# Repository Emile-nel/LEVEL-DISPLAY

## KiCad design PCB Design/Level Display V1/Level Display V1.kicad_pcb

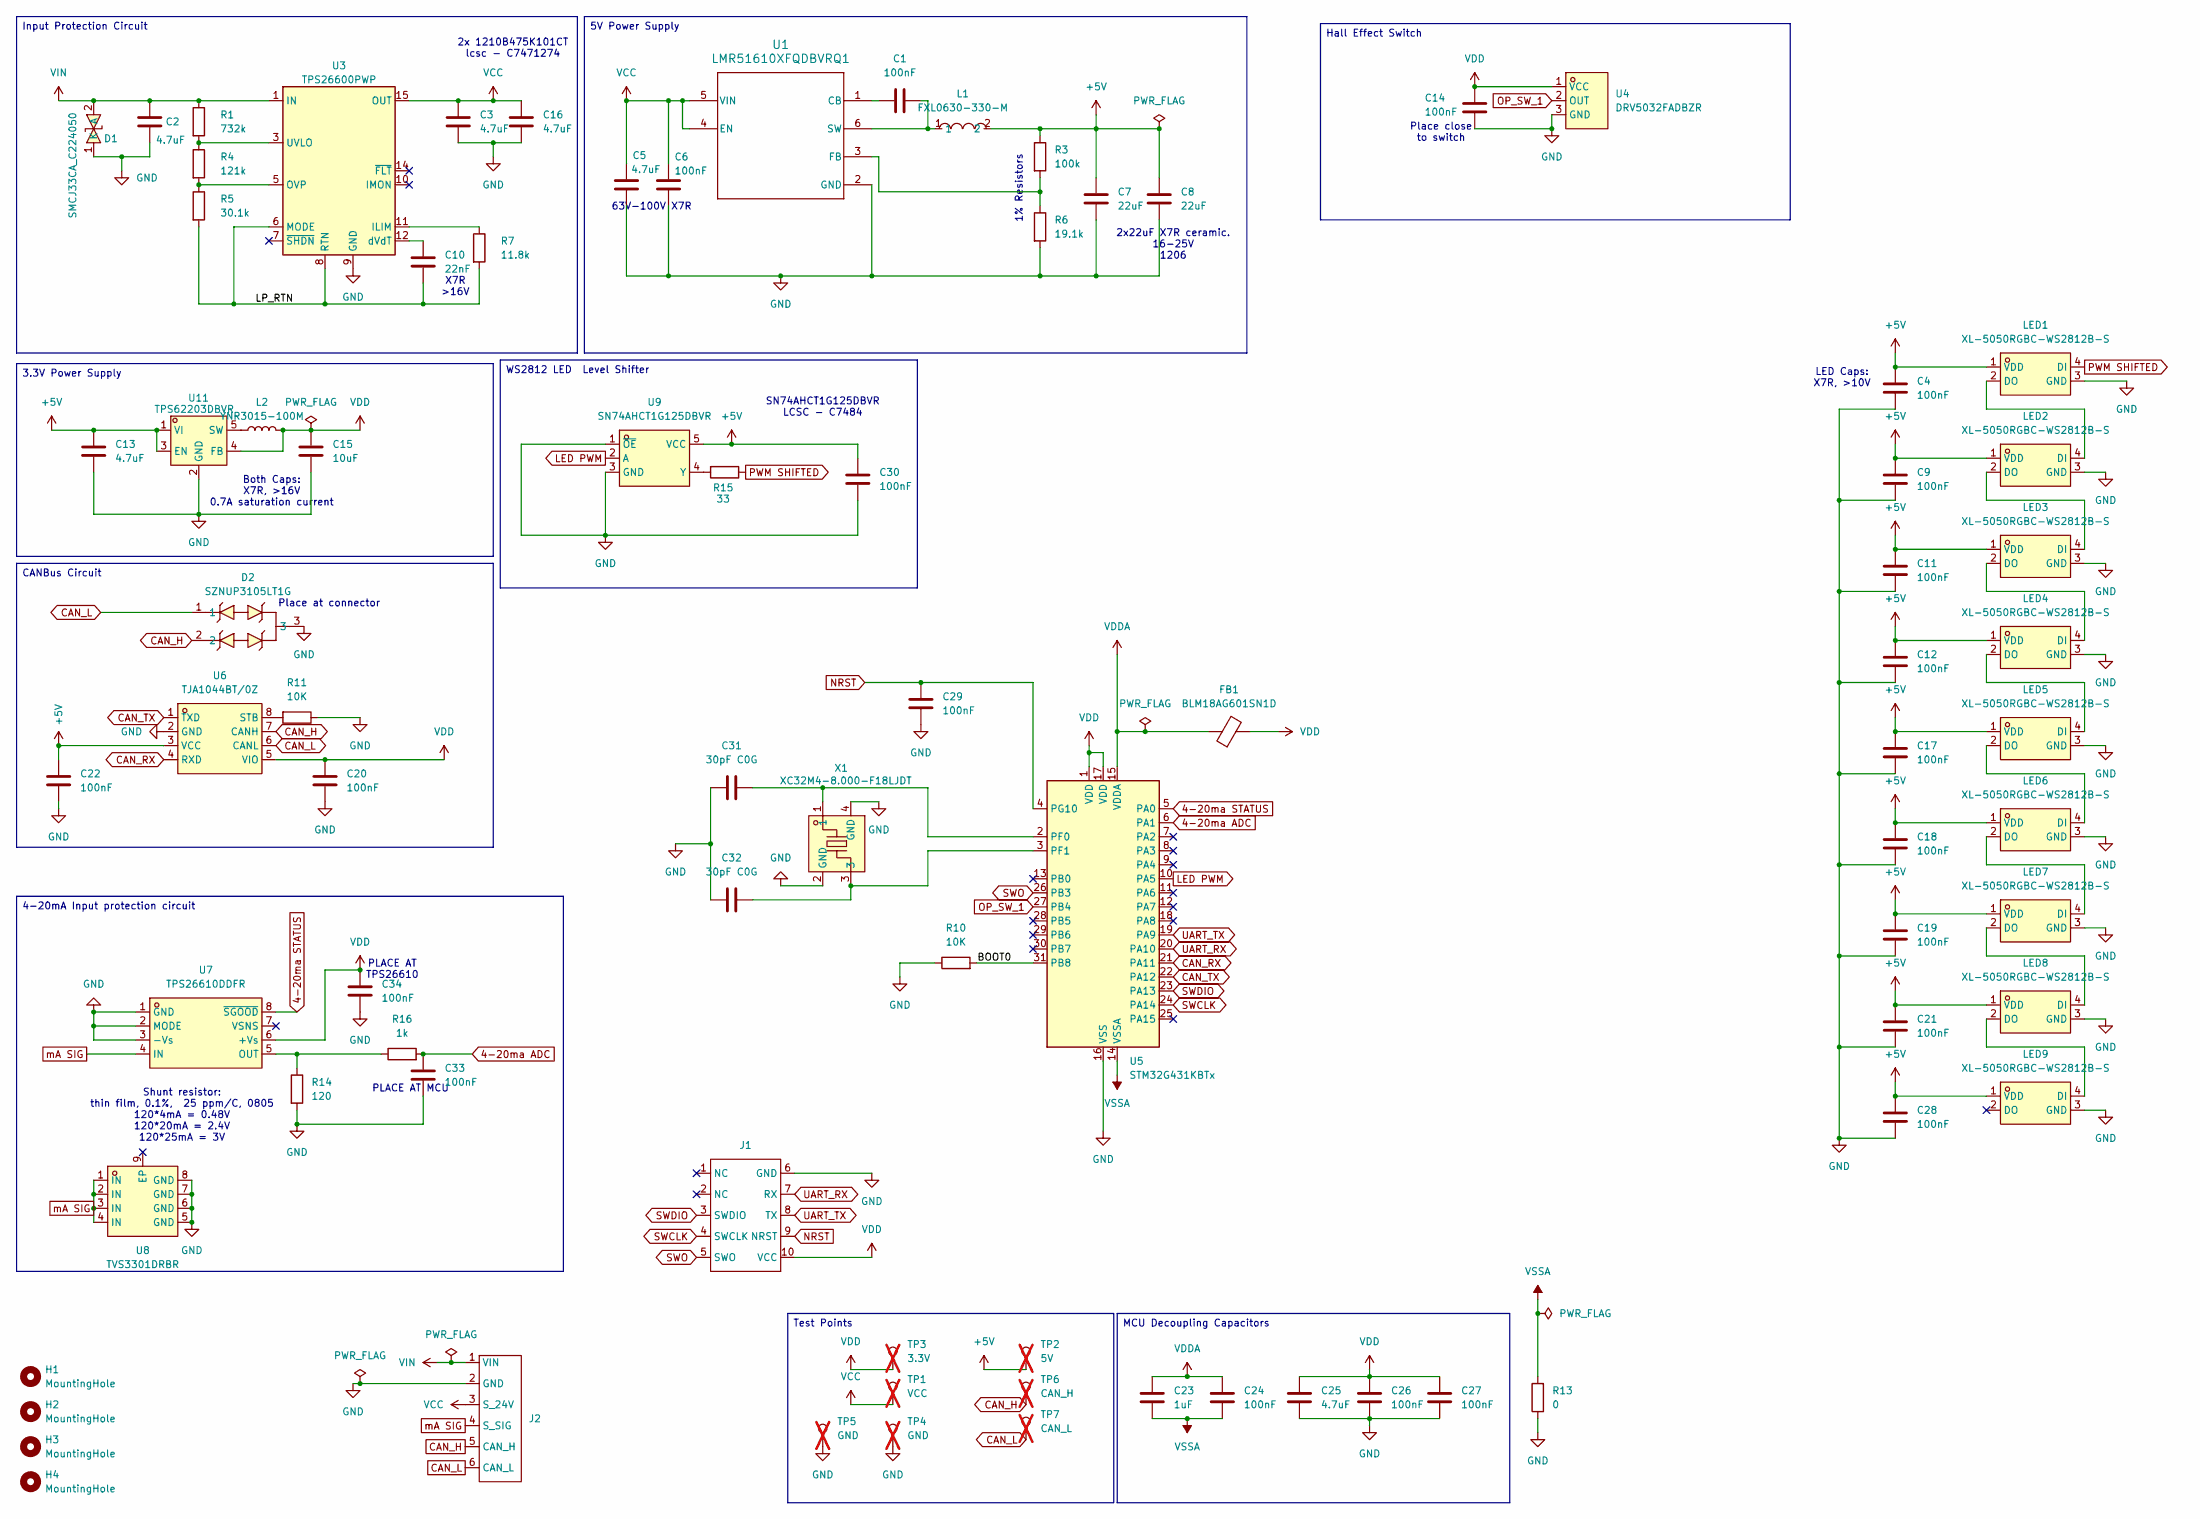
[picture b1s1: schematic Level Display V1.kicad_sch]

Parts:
C1, C4, C6, C9, C11, C12, C14, C17, C18, C19, C20, C21, C22, C24, C26, C27, C28, C29, C30, C33, C34: 100nF; C_0603_1608Metric; LCSC Part C14663
C2, C3, C5, C16: 4.7uF; C_1206_3216Metric; LCSC Part C29823
C7, C8: 22uF; C_1206_3216Metric; LCSC Part C12891
C10: 22nF; C_0805_2012Metric; LCSC Part C1729
C13, C25: 4.7uF; C_0603_1608Metric; LCSC Part C19666
C15: 10uF; C_0805_2012Metric; LCSC Part C15850
C23: 1uF; C_0603_1608Metric; LCSC Part C15849
C31, C32: 30pF C0G; C_0603_1608Metric; LCSC Part C1658
D1: SMCJ33CA_C224050; SMC_L6.9-W5.9-LS7.9-BI; MPN SMCJ33CA; LCSC Part C224050
D2: SZNUP3105LT1G; SOT-23-3_L2.9-W1.3-P1.90-LS2.4-BR; MPN SZNUP3105LT1G; LCSC Part C233434
FB1: BLM18AG601SN1D; L_0603_1608Metric; LCSC Part C19330
H1, H2, H3, H4: MountingHole; MountingHole_2.2mm_M2_DIN965_Pad_TopBottom
J1: CONN_STLINK-V3-MINIE
J2: LEAD_PAD_6_V2
L1: FXL0630-330-M; IND-SMD_L7.0-W6.6_FXL0630; MPN FXL0630-330-M; LCSC Part C177245
L2: YNR3015-100M; IND-SMD_L3.0-W3.0-1; LCSC Part C340363
LED1, LED2, LED3, LED4, LED5, LED6, LED7, LED8, LED9: XL-5050RGBC-WS2812B-S; LED-SMD_4P-L5.0-W5.0-TL-1; MPN XL-5050RGBC-2812B-S; LCSC Part C22461793
R1: 732k; R_0603_1608Metric; LCSC Part C23239
R3: 100k; R_0603_1608Metric; LCSC Part C25803
R4: 121k; R_0603_1608Metric; LCSC Part C25809
R5: 30.1k; R_0603_1608Metric; LCSC Part C23000
R6: 19.1k; R_0603_1608Metric; LCSC Part C22897
R7: 11.8k; R_0603_1608Metric; LCSC Part C22861
R10, R11: 10K; R_0603_1608Metric; LCSC Part C25804
R13: 0; R_0603_1608Metric; LCSC Part C21189
R14: 120; R_0805_2012Metric; LCSC Part C865162
R15: 33; R_0603_1608Metric; LCSC Part C23140
R16: 1k; R_0805_2012Metric; LCSC Part C17513
TP1: VCC; TestPoint_Pad_D1.5mm; not fitted
TP2: 5V; TestPoint_Pad_D1.5mm; not fitted
TP3: 3.3V; TestPoint_Pad_D1.5mm; not fitted
TP4, TP5: GND; TestPoint_Pad_D1.5mm; not fitted
TP6: CAN_H; TestPoint_Pad_D1.5mm; not fitted
TP7: CAN_L; TestPoint_Pad_D1.5mm; not fitted
U1: LMR51610XFQDBVRQ1; SOT-23-6_L2.9-W1.6-P0.95-LS2.8-BL-2; LCSC Part C41707191
U3: TPS26600PWP; HTSSOP-16-1EP_4.4x5mm_P0.65mm_EP3.4x5mm_Mask2.66x2.46mm_The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; LCSC Part C544399
U4: DRV5032FADBZR; SOT-23-3_L2.9-W1.3-P0.95-LS2.4-BR; MPN DRV5032FADBZR; LCSC Part C140921
U5: STM32G431KBTx; LQFP-32_7x7mm_P0.8mm; LCSC Part C529357
U6: TJA1044BT/0Z; SOIC-8_L4.9-W3.9-P1.27-LS6.0-BL; MPN TJA1044BT/0Z; LCSC Part C20234933
U7: TPS26610DDFR; TSOT-23-8_L2.9-W1.6-P0.65-LS2.8-BR; MPN TPS26610DDFR; LCSC Part C3194314
U8: TVS3301DRBR; VSON-8_L3.0-W3.0-P0.65-BL-EP; MPN TVS3301DRBR; LCSC Part C2864392
U9: SN74AHCT1G125DBVR; SOT-23-5_L3.0-W1.7-P0.95-LS2.8-BR; MPN SN74AHCT1G125DBVR; LCSC Part C7484
U11: TPS62203DBVR; SOT-23-5_L3.0-W1.7-P0.95-LS2.8-BR; MPN TPS62203DBVR; LCSC Part C9051
X1: XC32M4-8.000-F18LJDT; CRYSTAL-SMD_4P-L3.2-W2.5-BL; MPN XC32M4-8.000-F18LJDT; LCSC Part C2905353

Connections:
4-20ma ADC: C33.1, R16.2, U5.6 (PA1)
4-20ma STATUS: U5.5 (PA0), U7.8 (~SGOOD)
+5V: C4.1, C7.2, C8.2, C9.1, C11.1, C12.1, C13.1, C17.1, C18.1, C19.1, C21.1, C22.1, C28.1, C30.1, L1.2, LED1.1 (VDD), LED2.1 (VDD), LED3.1 (VDD), LED4.1 (VDD), LED5.1 (VDD), LED6.1 (VDD), LED7.1 (VDD), LED8.1 (VDD), LED9.1 (VDD), R3.1, TP2.1 (1_1), U6.3 (VCC), U9.5 (VCC), U11.1 (VI), U11.3 (EN)
/BOOT0: R10.2, U5.31 (PB8)
/LP_RTN: C10.2, R5.2, R7.2, U3.6 (MODE), U3.8 (RTN), U3.17 (RTN)
CAN_H: D2.2, J2.5 (CAN_H), TP6.1 (1_1), U6.7 (CANH)
CAN_L: D2.1, J2.6 (CAN_L), TP7.1 (1_1), U6.6 (CANL)
CAN_RX: U5.21 (PA11), U6.4 (RXD)
CAN_TX: U5.22 (PA12), U6.1 (TXD)
GND: C2.2, C3.2, C4.2, C5.2, C6.2, C7.1, C8.1, C9.2, C11.2, C12.2, C13.2, C14.2, C15.2, C16.2, C17.2, C18.2, C19.2, C20.2, C21.2, C22.2, C25.2, C26.2, C27.2, C28.2, C29.2, C30.2, C31.1, C32.1, C33.2, C34.2, D1.1 (K), D2.3, J1.6 (GND), J2.2 (GND), LED1.3 (GND), LED2.3 (GND), LED3.3 (GND), LED4.3 (GND), LED5.3 (GND), LED6.3 (GND), LED7.3 (GND), LED8.3 (GND), LED9.3 (GND), R6.2, R10.1, R11.1, R13.1, R14.2, TP4.1 (1_1), TP5.1 (1_1), U1.2 (GND), U3.9 (GND), U4.3 (GND), U5.16 (VSS), U5.32 (VSS), U6.2 (GND), U7.1 (GND), U7.2 (MODE), U7.3 (-Vs), U8.5 (GND), U8.6 (GND), U8.7 (GND), U8.8 (GND), U9.1 (~OE), U9.3 (GND), U11.2 (GND), X1.2 (GND), X1.4 (GND)
LED PWM: U5.10 (PA5), U9.2 (A)
NRST: C29.1, J1.9 (NRST), U5.4 (PG10)
unnamed: LED1.2 (DO), LED2.4 (DI)
unnamed: LED2.2 (DO), LED3.4 (DI)
unnamed: LED3.2 (DO), LED4.4 (DI)
unnamed: LED4.2 (DO), LED5.4 (DI)
unnamed: LED5.2 (DO), LED6.4 (DI)
unnamed: LED6.2 (DO), LED7.4 (DI)
unnamed: LED7.2 (DO), LED8.4 (DI)
unnamed: LED8.2 (DO), LED9.4 (DI)
unnamed: C1.1, U1.1 (CB)
unnamed: R3.2, R6.1, U1.3 (FB)
unnamed: C1.2, L1.1, U1.6 (SW)
unnamed: R7.1, U3.11 (ILIM)
unnamed: R4.2, R5.1, U3.5 (OVP)
unnamed: R1.2, R4.1, U3.3 (UVLO)
unnamed: C10.1, U3.12 (dVdT)
unnamed: C31.2, U5.2 (PF0), X1.1
unnamed: C32.2, U5.3 (PF1), X1.3
unnamed: R11.2, U6.8 (STB)
unnamed: R14.1, R16.1, U7.5 (OUT)
unnamed: R15.2, U9.4 (Y)
unnamed: L2.1, U11.5 (SW)
OP_SW_1: U4.2 (OUT), U5.27 (PB4)
PWM SHIFTED: LED1.4 (DI), R15.1
SWCLK: J1.4 (SWCLK), U5.24 (PA14)
SWDIO: J1.3 (SWDIO), U5.23 (PA13)
SWO: J1.5 (SWO), U5.26 (PB3)
UART_RX: J1.7 (RX), U5.20 (PA10)
UART_TX: J1.8 (TX), U5.19 (PA9)
VCC: C3.1, C5.1, C6.1, C16.1, J2.3 (S_24V), TP1.1 (1_1), U1.4 (EN), U1.5 (VIN), U3.15 (OUT), U3.16 (OUT)
VDD: C14.1, C15.1, C20.1, C25.1, C26.1, C27.1, C34.1, FB1.2, J1.10 (VCC), L2.2, TP3.1 (1_1), U4.1 (VCC), U5.1 (VDD), U5.17 (VDD), U6.5 (VIO), U7.6 (+Vs), U11.4 (FB)
VDDA: C23.1, C24.1, FB1.1, U5.15 (VDDA)
VIN: C2.1, D1.2 (A), J2.1 (VIN), R1.1, U3.1 (IN), U3.2 (IN)
VSSA: C23.2, C24.2, R13.2, U5.14 (VSSA)
mA SIG: J2.4 (S_SIG), U7.4 (IN), U8.1 (IN), U8.2 (IN), U8.3 (IN), U8.4 (IN)

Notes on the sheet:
1% Resistors
Both Caps: X7R, >16V 0.7A saturation current
LED Caps: X7R, >10V
PLACE AT TPS26610
Place at connector
63V-100V X7R
Place close to switch
Shunt resistor: thin film, 0.1%, 25 ppm/C, 0805 120*4mA = 0.48V 120*20mA = 2.4V 120*25mA = 3V
X7R >16V
2x 1210B475K101CT lcsc - C7471274
PLACE AT MCU
SN74AHCT1G125DBVR LCSC - C7484
2x22uF X7R ceramic. 16-25V 1206
3.3V Power Supply
CANBus Circuit
5V Power Supply
Input Protection Circuit
WS2812 LED Level Shifter
MCU Decoupling Capacitors
4-20mA Input protection circuit
Hall Effect Switch
Test Points

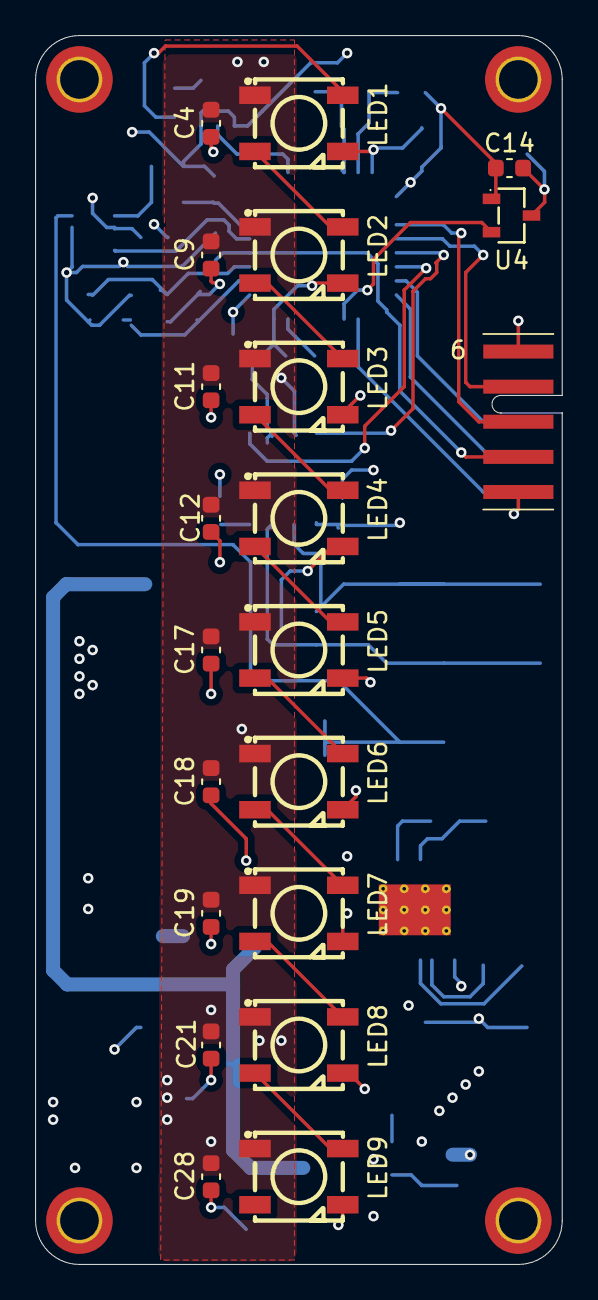
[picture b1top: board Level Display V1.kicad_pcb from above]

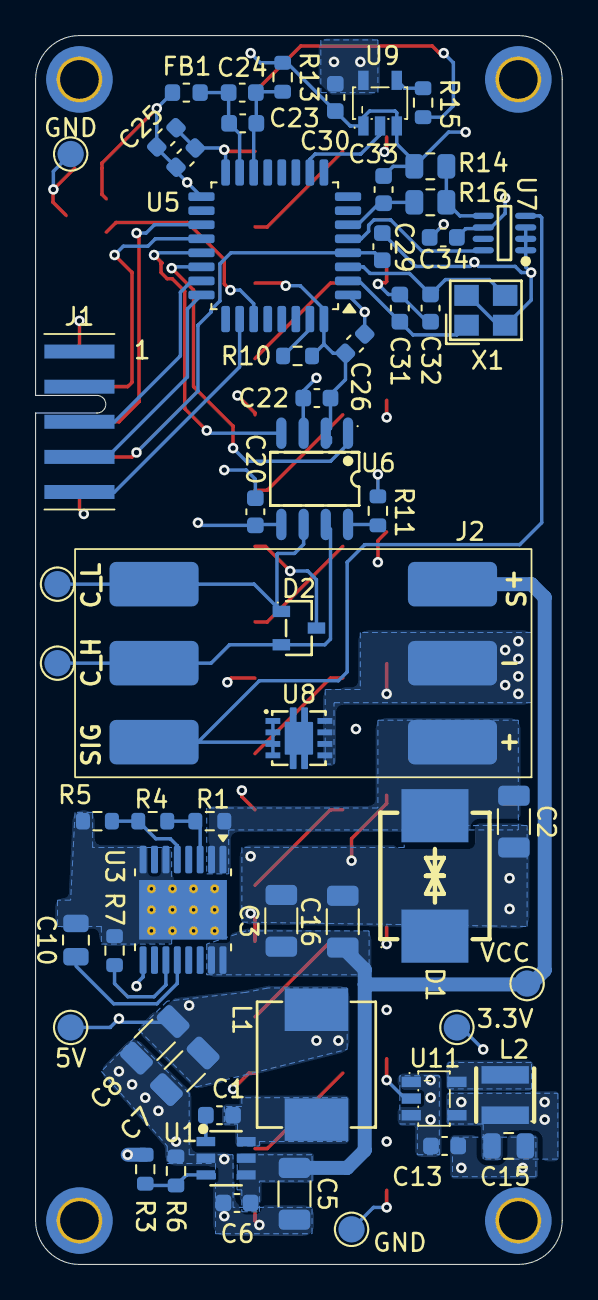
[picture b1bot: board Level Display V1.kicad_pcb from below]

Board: 4 copper layers, 30.0 x 70.0 mm, 83 parts (59 on the bottom side), 46 nets.

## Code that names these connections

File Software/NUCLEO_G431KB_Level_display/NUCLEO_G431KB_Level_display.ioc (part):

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Mcu.Name=STM32G431K(6-8-B)Tx
Mcu.Package=LQFP32
Mcu.UserName=STM32G431KBTx
PA0.Mode=IN1-Single-Ended
PA0.Signal=ADC2_IN1
PA1.Mode=IN2-Single-Ended
PA1.Signal=ADC2_IN2
PA13.GPIOParameters=GPIO_Label
PA13.GPIO_Label=T_SWDIO
PA13.Mode=Trace_Asynchronous_SW
PA13.Signal=SYS_JTMS-SWDIO
PA14.GPIOParameters=GPIO_Label
PA14.GPIO_Label=T_SWCLK
PA14.Mode=Trace_Asynchronous_SW
PA14.Signal=SYS_JTCK-SWCLK
PA2.Signal=USART2_TX
PA3.Signal=USART2_RX
PA9.Signal=S_TIM2_CH3
PB3.GPIOParameters=GPIO_Label
PB3.GPIO_Label=T_SWO
PB3.Mode=Trace_Asynchronous_SW
PB3.Signal=SYS_JTDO-SWO
PB4.Signal=GPIO_Input
PB5.Signal=GPIO_Input
RCC.HSE_VALUE=8000000
RCC.SYSCLKFreq_VALUE=160000000
RCC.SYSCLKSource=RCC_SYSCLKSOURCE_PLLCLK
board=NUCLEO-G431KB
boardIOC=true
